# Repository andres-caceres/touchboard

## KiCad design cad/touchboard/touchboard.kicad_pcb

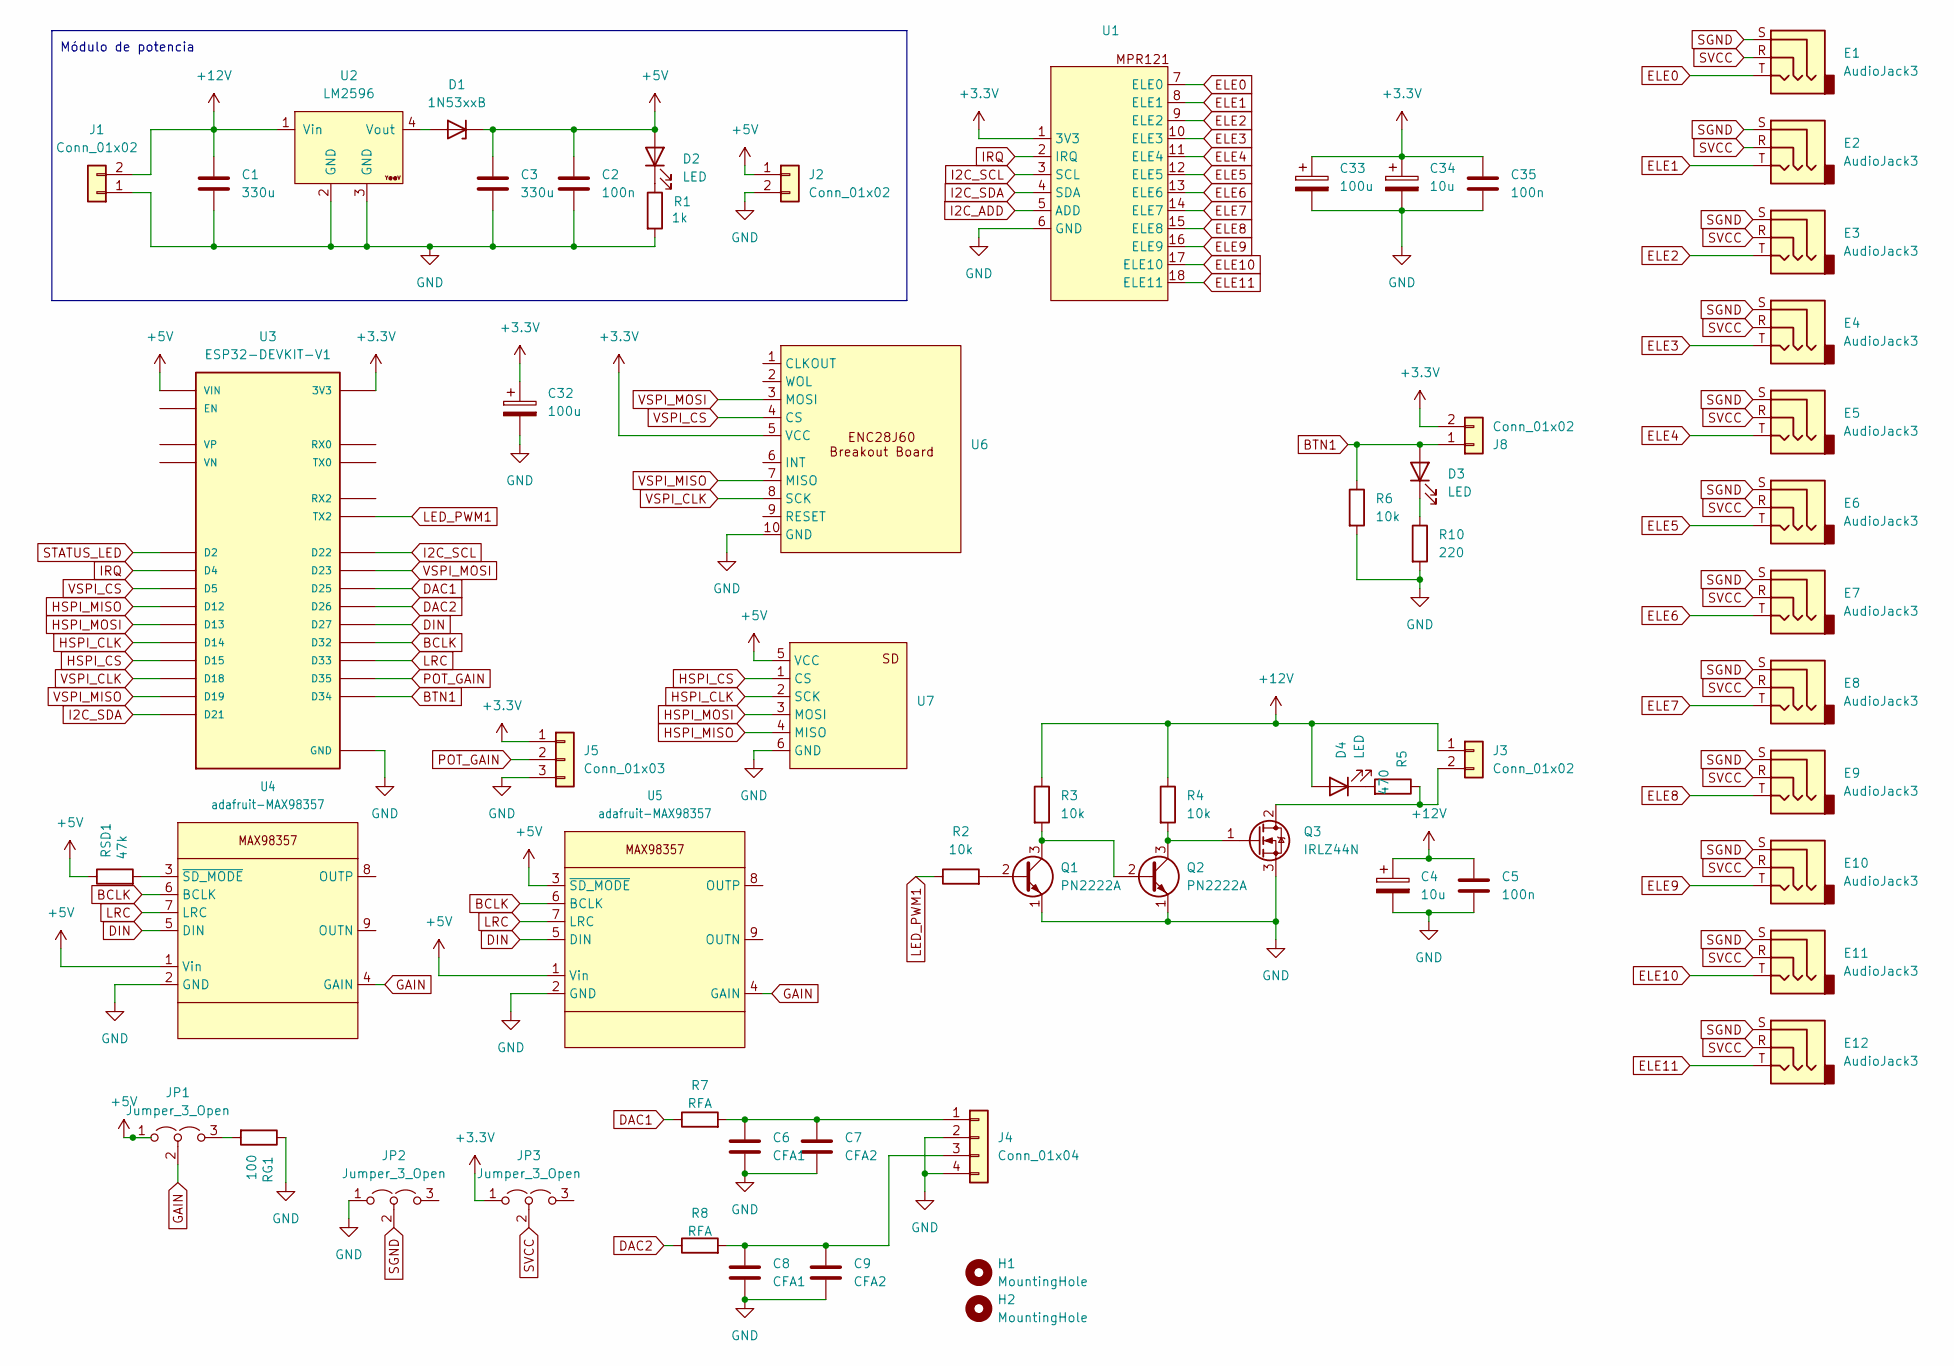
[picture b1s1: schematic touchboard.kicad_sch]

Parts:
C1, C3: 330u; CP_Radial_D8.0mm_P3.50mm
C2, C5, C35: 100n; C_Disc_D3.8mm_W2.6mm_P2.50mm
C4, C34: 10u; CP_Radial_D4.0mm_P1.50mm
C6, C8: CFA1; CP_Radial_D4.0mm_P1.50mm
C7, C9: CFA2; C_Disc_D3.8mm_W2.6mm_P2.50mm
C32, C33: 100u; CP_Radial_D6.3mm_P2.50mm
D1: 1N53xxB; D_DO-201_P15.24mm_Horizontal
D2: LED; LED_D5.0mm
D3, D4: LED; LED_D3.0mm
E1, E2, E3, E4, E5, E6, E7, E8, E9, E10, E11, E12: AudioJack3; Jack_3.5mm_CUI_SJ-3523-SMT_Horizontal
H1, H2: MountingHole; MountingHole_3.2mm_M3
J1, J3: Conn_01x02; PhoenixContact_MSTBA_2,5_2-G_1x02_P5.00mm_Horizontal
J2, J8: Conn_01x02; JST_EH_B2B-EH-A_1x02_P2.50mm_Vertical
J4: Conn_01x04; JST_EH_B4B-EH-A_1x04_P2.50mm_Vertical
J5: Conn_01x03; JST_EH_B3B-EH-A_1x03_P2.50mm_Vertical
JP1, JP2, JP3: Jumper_3_Open; PinHeader_1x03_P2.54mm_Vertical
Q1, Q2: PN2222A; TO-92_Inline
Q3: IRLZ44N; TO-220-3_Vertical
R1: 1k; R_Axial_DIN0207_L6.3mm_D2.5mm_P7.62mm_Horizontal
R2, R3, R4, R6: 10k; R_Axial_DIN0207_L6.3mm_D2.5mm_P7.62mm_Horizontal
R5: 470; R_Axial_DIN0207_L6.3mm_D2.5mm_P7.62mm_Horizontal
R7, R8: RFA; R_Axial_DIN0207_L6.3mm_D2.5mm_P7.62mm_Horizontal
R10: 220; R_Axial_DIN0207_L6.3mm_D2.5mm_P7.62mm_Horizontal
RG1: 100; R_Axial_DIN0207_L6.3mm_D2.5mm_P7.62mm_Horizontal
RSD1: 47k; R_Axial_DIN0207_L6.3mm_D2.5mm_P7.62mm_Horizontal
U1: MPR121
U2: LM2596; YAAJ_DCDC_StepDown_LM2596
U3: ESP32-DEVKIT-V1; MODULE_ESP32_DEVKIT_V1; PARTREV N/A
U4, U5: adafruit-MAX98357
U6: ENC28J60
U7: SD_module

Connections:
+3.3V: C32.1, C33.1, C34.1, C35.1, J5.1, J8.2, JP3.1 (A), U1.1 (3V3), U3.1 (3V3), U6.5 (VCC)
+5V: C2.1, C3.1, D1.1 (K), D2.2 (A), J2.1, JP1.1 (A), RSD1.1, U3.30 (VIN), U4.1 (Vin), U5.1 (Vin), U5.3 (~SD_MODE), U7.5 (VCC)
+12V: C1.1, C4.1, C5.1, D4.2 (A), J1.2, J3.1, R3.1, R4.1, U2.1 (Vin)
BCLK: U3.21 (D32), U4.6 (BCLK), U5.6 (BCLK)
BTN1: D3.2 (A), J8.1, R6.1, U3.19 (D34)
DAC1: R7.1, U3.23 (D25)
DAC2: R8.1, U3.24 (D26)
DIN: U3.25 (D27), U4.5 (DIN), U5.5 (DIN)
ELE0: E1.T, U1.7 (ELE0)
ELE1: E2.T, U1.8 (ELE1)
ELE2: E3.T, U1.9 (ELE2)
ELE3: E4.T, U1.10 (ELE3)
ELE4: E5.T, U1.11 (ELE4)
ELE5: E6.T, U1.12 (ELE5)
ELE6: E7.T, U1.13 (ELE6)
ELE7: E8.T, U1.14 (ELE7)
ELE8: E9.T, U1.15 (ELE8)
ELE9: E10.T, U1.16 (ELE9)
ELE10: E11.T, U1.17 (ELE10)
ELE11: E12.T, U1.18 (ELE11)
GAIN: JP1.2 (C), U4.4 (GAIN), U5.4 (GAIN)
GND: C1.2, C2.2, C3.2, C4.2, C5.2, C6.2, C7.2, C8.2, C9.2, C32.2, C33.2, C34.2, C35.2, J1.1, J2.2, J4.2, J4.4, J5.3, JP2.1 (A), Q1.1 (E), Q2.1 (E), Q3.3 (S), R1.2, R6.2, R10.2, RG1.1, U1.6 (GND), U2.2 (GND), U2.3 (GND), U3.2 (GND), U3.29 (GND), U4.2 (GND), U5.2 (GND), U6.10 (GND), U7.6 (GND)
HSPI_CLK: U3.26 (D14), U7.2 (SCK)
HSPI_CS: U3.3 (D15), U7.1 (CS)
HSPI_MISO: U3.27 (D12), U7.4 (MISO)
HSPI_MOSI: U3.28 (D13), U7.3 (MOSI)
I2C_ADD: U1.5 (ADD)
I2C_SCL: U1.3 (SCL), U3.14 (D22)
I2C_SDA: U1.4 (SDA), U3.11 (D21)
IRQ: U1.2 (IRQ), U3.5 (D4)
LED_PWM1: R2.1, U3.7 (TX2)
LRC: U3.22 (D33), U4.7 (LRC), U5.7 (LRC)
unnamed: D1.2 (A), U2.4 (Vout)
unnamed: D2.1 (K), R1.1
unnamed: D3.1 (K), R10.1
unnamed: D4.1 (K), R5.2
unnamed: J3.2, Q3.2 (D), R5.1
unnamed: C6.1, C7.1, J4.1, R7.2
unnamed: C8.1, C9.1, J4.3, R8.2
unnamed: JP1.3 (B), RG1.2
unnamed: Q1.2 (B), R2.2
unnamed: Q1.3 (C), Q2.2 (B), R3.2
unnamed: Q2.3 (C), Q3.1 (G), R4.2
unnamed: RSD1.2, U4.3 (~SD_MODE)
POT_GAIN: J5.2, U3.20 (D35)
SGND: E1.S, E2.S, E3.S, E4.S, E5.S, E6.S, E7.S, E8.S, E9.S, E10.S, E11.S, E12.S, JP2.2 (C)
STATUS_LED: U3.4 (D2)
SVCC: E1.R, E2.R, E3.R, E4.R, E5.R, E6.R, E7.R, E8.R, E9.R, E10.R, E11.R, E12.R, JP3.2 (C)
VSPI_CLK: U3.9 (D18), U6.8 (SCK)
VSPI_CS: U3.8 (D5), U6.4 (CS)
VSPI_MISO: U3.10 (D19), U6.7 (MISO)
VSPI_MOSI: U3.15 (D23), U6.3 (MOSI)

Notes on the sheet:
Módulo de potencia

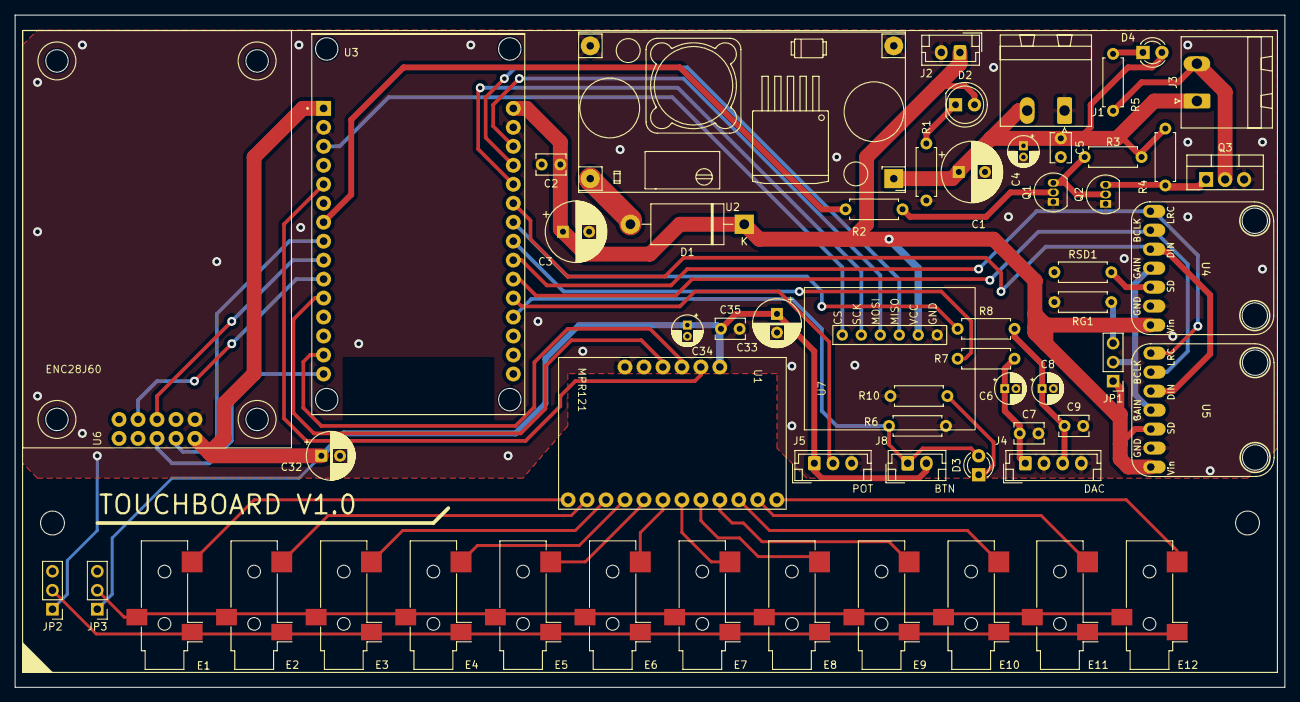
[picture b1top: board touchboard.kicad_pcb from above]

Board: 2 copper layers, 170.0 x 90.0 mm, 61 parts (0 on the bottom side), 50 nets.

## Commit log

2024-10-12 add firmware
2024-10-15 cad added
2024-10-15 designed pcb
2024-10-15 pcb done
2024-10-15 bck update
2024-10-16 pcb board update
2024-10-16 touchboard pcb cad v1 finished
2024-10-16 firmware test
2024-10-16 added test files
2024-10-16 Ethernet test done
